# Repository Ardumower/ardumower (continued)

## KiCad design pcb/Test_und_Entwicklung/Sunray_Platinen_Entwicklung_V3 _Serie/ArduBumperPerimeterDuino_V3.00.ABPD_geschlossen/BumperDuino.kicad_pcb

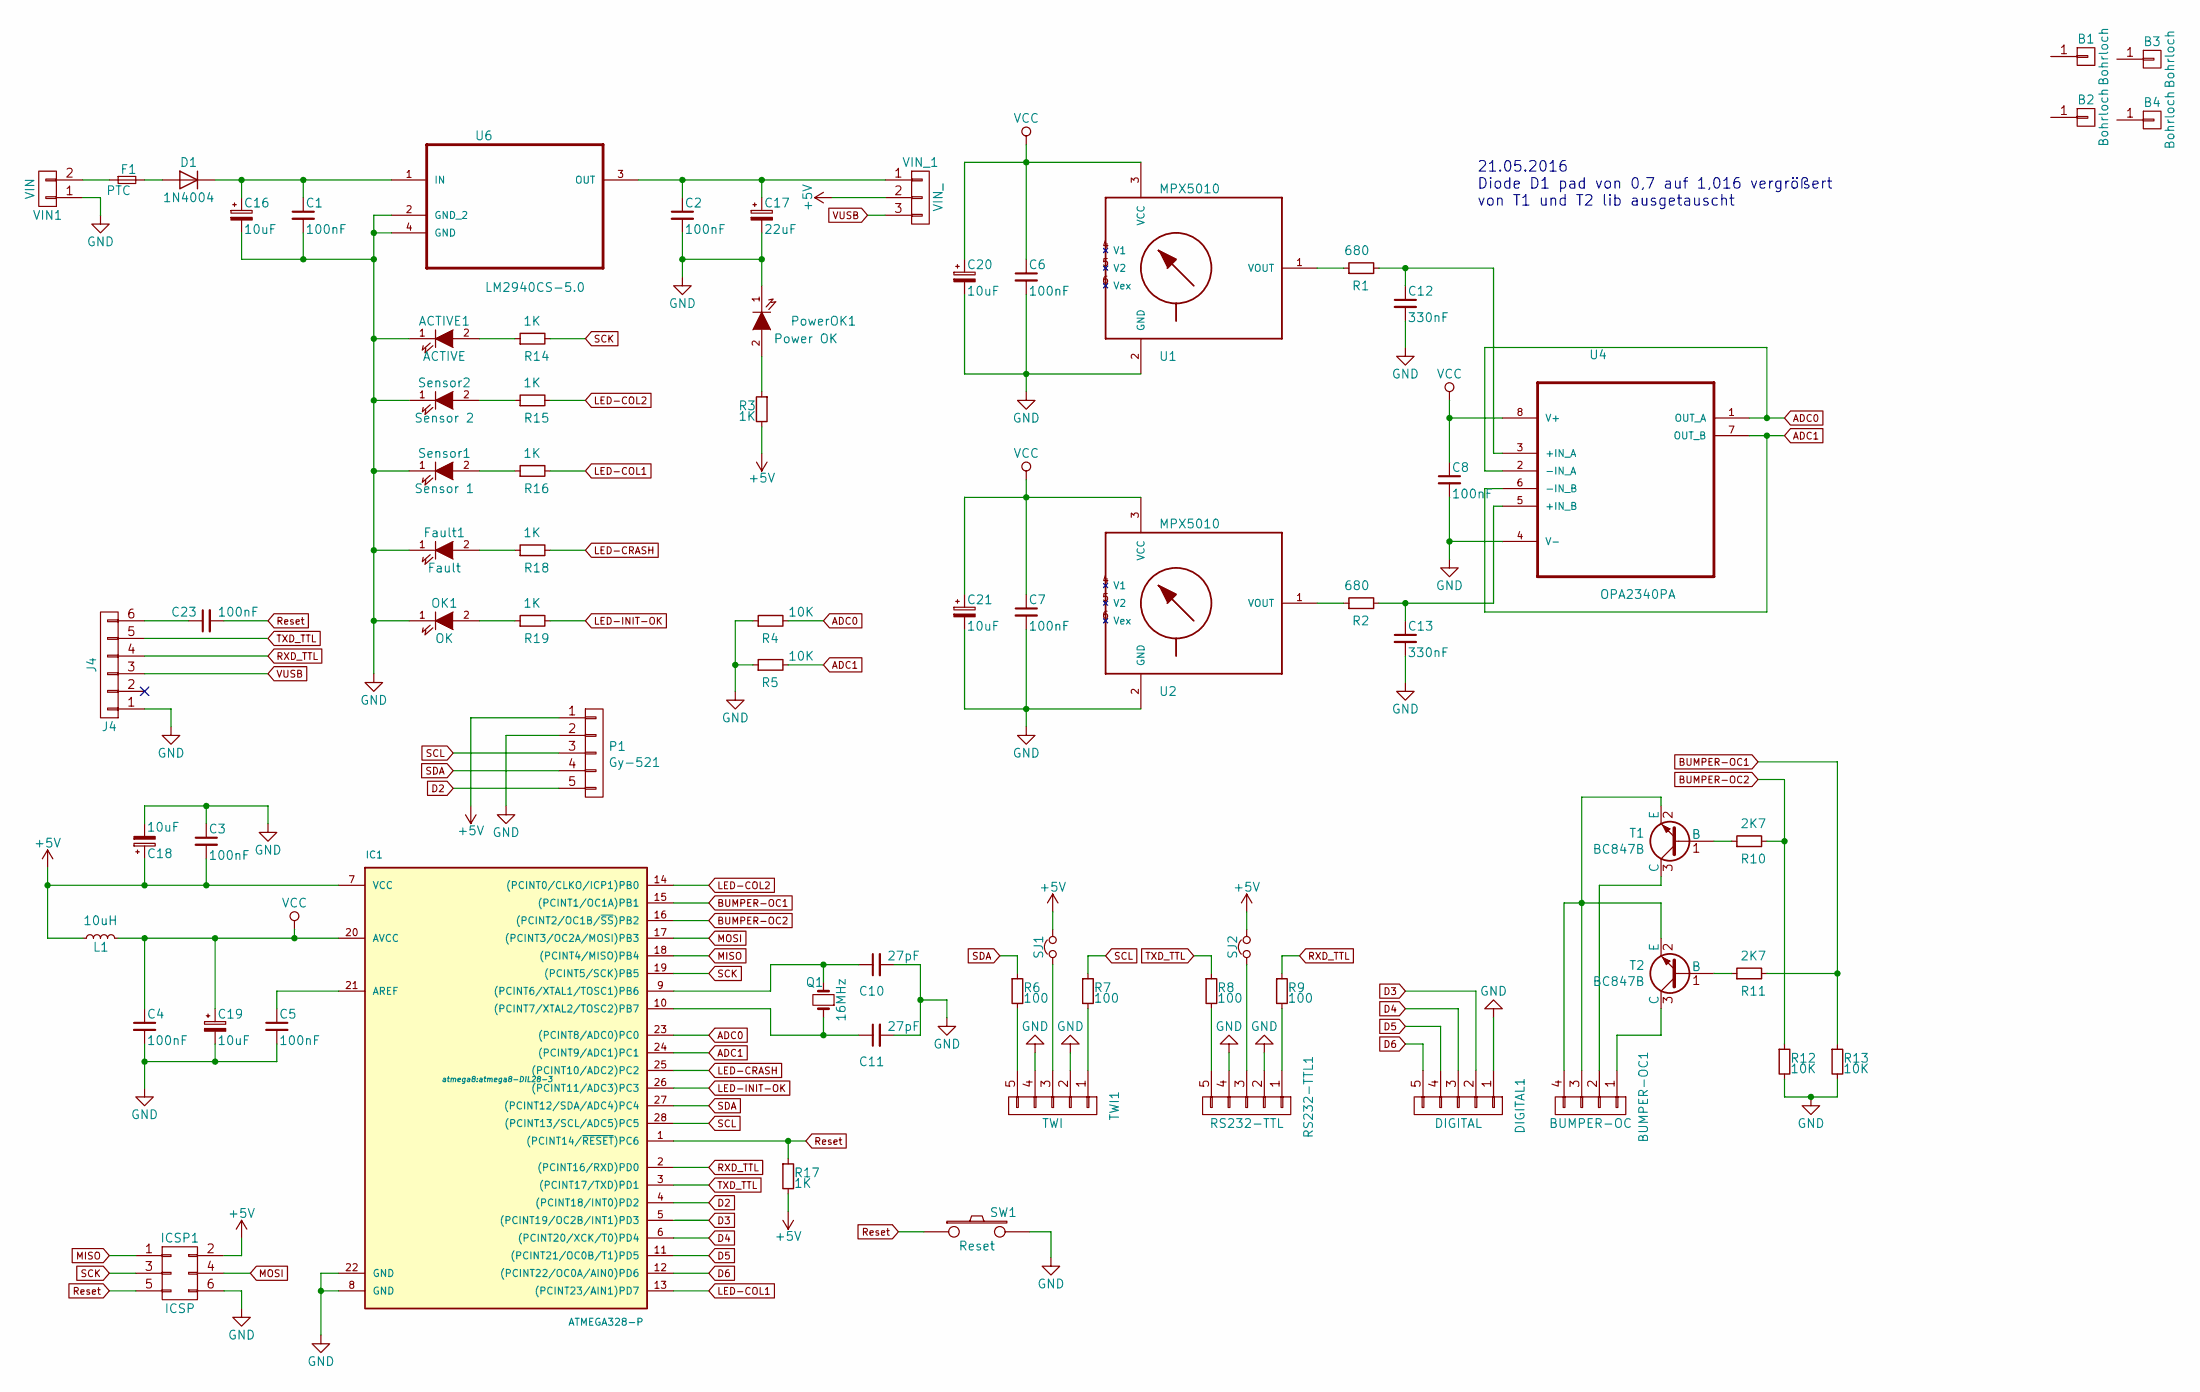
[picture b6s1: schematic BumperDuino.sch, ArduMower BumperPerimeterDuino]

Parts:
ACTIVE1: ACTIVE; LED_1206
B1, B2, B3, B4: Bohrloch; Bohrloch_3,2mm
BUMPER-OC1: BUMPER-OC; Pin_Header_Straight_1x04
C1, C2, C3, C4, C5, C6, C7, C8, C23: 100nF; C_0805
C10, C11: 27pF; C_0805
C12, C13: 330nF; C_0805
C16, C18, C19, C20, C21: 10uF; Elko_vert_11x5mm_RM2.5
C17: 22uF; Elko_vert_11x5mm_RM2.5
D1: 1N4004; Diode_DO-35_SOD27_Horizontal_RM10
DIGITAL1: DIGITAL; Pin_Header_Straight_1x05
F1: PTC; Fuse_SMD
Fault1: Fault; LED_1206
IC1: ATMEGA328-P; atmega8-DIL28-3
ICSP1: ICSP; Pin_Header_Straight_2x03
J4: J4; Pin_Header_Straight_1x06
L1: 10uH; Resistor_Horizontal_RM10mm
OK1: OK; LED_1206
P1: Gy-521; Pin_Header_Straight_1x05
PowerOK1: Power OK; LED_1206
Q1: 16MHz; Crystal_HC49-U_Vertical
R1, R2: 680; R_1206
R3, R14, R15, R16, R17, R18, R19: 1K; R_1206
R4, R5, R12, R13: 10K; R_1206
R6, R7, R8, R9: 100; R_1206
R10, R11: 2K7; R_1206
RS232-TTL1: RS232-TTL; Pin_Header_Straight_1x05
SJ1, SJ2: Jumper_NC_Small; Pin_Header_Straight_1x02
SW1: Reset; SW_SPST_FSMSM
Sensor1: Sensor 1; LED_1206
Sensor2: Sensor 2; LED_1206
T1, T2: BC847B; SOT-23
TWI1: TWI; Pin_Header_Straight_1x05
U1, U2: MPX5010; 867C-H
U4: OPA2340PA; DIP254P762X508-8
U6: LM2940CS-5.0; TO254P1435X464-4N
VIN1: VIN; Pin_Header_Straight_1x02
VIN_1: VIN_; Pin_Header_Straight_1x03

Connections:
+5V: C3.2, C18.1, IC1.7 (VCC), ICSP1.2, L1.1, P1.1, R3.2, R17.2, SJ1.2, SJ2.2, VIN_1.2
ADC0: IC1.23 ((PCINT8/ADC0)PC0), R4.2, U4.1 (OUT_A), U4.2 (-IN_A)
ADC1: IC1.24 ((PCINT9/ADC1)PC1), R5.2, U4.6 (-IN_B), U4.7 (OUT_B)
BUMPER-OC1: IC1.15 ((PCINT1/OC1A)PB1), R11.2, R13.1
BUMPER-OC2: IC1.16 ((PCINT2/OC1B/~SS~)PB2), R10.2, R12.1
D2: IC1.4 ((PCINT18/INT0)PD2), P1.5
D3: DIGITAL1.2, IC1.5 ((PCINT19/OC2B/INT1)PD3)
D4: DIGITAL1.3, IC1.6 ((PCINT20/XCK/T0)PD4)
D5: DIGITAL1.4, IC1.11 ((PCINT21/OC0B/T1)PD5)
D6: DIGITAL1.5, IC1.12 ((PCINT22/OC0A/AIN0)PD6)
GND: ACTIVE1.1 (K), C1.2, C2.2, C3.1, C4.2, C5.2, C6.2, C7.2, C8.2, C10.2, C11.2, C12.2, C13.2, C16.2, C17.2, C18.2, C19.2, C20.2, C21.2, DIGITAL1.1, Fault1.1 (K), IC1.8 (GND), IC1.22 (GND), ICSP1.6, J4.1, OK1.1 (K), P1.2, PowerOK1.1 (K), R4.1, R5.1, R12.2, R13.2, RS232-TTL1.2, RS232-TTL1.4, SW1.2, Sensor1.1 (K), Sensor2.1 (K), TWI1.2, TWI1.4, U1.2 (GND), U2.2 (GND), U4.4 (V-), U6.2 (GND_2), U6.4 (GND), VIN1.1
LED-COL1: IC1.13 ((PCINT23/AIN1)PD7), R16.2
LED-COL2: IC1.14 ((PCINT0/CLKO/ICP1)PB0), R15.2
LED-CRASH: IC1.25 ((PCINT10/ADC2)PC2), R18.2
LED-INIT-OK: IC1.26 ((PCINT11/ADC3)PC3), R19.2
MISO: IC1.18 ((PCINT4/MISO)PB4), ICSP1.1
MOSI: IC1.17 ((PCINT3/OC2A/MOSI)PB3), ICSP1.4
unnamed: ACTIVE1.2 (A), R14.1
unnamed: BUMPER-OC1.1, T2.3 (C)
unnamed: BUMPER-OC1.2, T1.3 (C)
unnamed: BUMPER-OC1.3, BUMPER-OC1.4, T1.2 (E), T2.2 (E)
unnamed: C1.1, C16.1, D1.1 (K), U6.1 (IN)
unnamed: C5.1, IC1.21 (AREF)
unnamed: C10.1, IC1.9 ((PCINT6/XTAL1/TOSC1)PB6), Q1.2
unnamed: C11.1, IC1.10 ((PCINT7/XTAL2/TOSC2)PB7), Q1.1
unnamed: C12.1, R1.2, U4.3 (+IN_A)
unnamed: C13.1, R2.2, U4.5 (+IN_B)
unnamed: C2.1, C17.1, U6.3 (OUT), VIN_1.1
unnamed: C23.1, J4.6
unnamed: D1.2 (A), F1.2
unnamed: F1.1, VIN1.2
unnamed: Fault1.2 (A), R18.1
unnamed: OK1.2 (A), R19.1
unnamed: PowerOK1.2 (A), R3.1
unnamed: R1.1, U1.1 (VOUT)
unnamed: R2.1, U2.1 (VOUT)
unnamed: R6.2, TWI1.5
unnamed: R7.2, TWI1.1
unnamed: R8.2, RS232-TTL1.5
unnamed: R9.2, RS232-TTL1.1
unnamed: R10.1, T1.1 (B)
unnamed: R11.1, T2.1 (B)
unnamed: R15.1, Sensor2.2 (A)
unnamed: R16.1, Sensor1.2 (A)
unnamed: RS232-TTL1.3, SJ2.1
unnamed: SJ1.1, TWI1.3
RXD_TTL: IC1.2 ((PCINT16/RXD)PD0), J4.4, R9.1
Reset: C23.2, IC1.1 ((PCINT14/~RESET~)PC6), ICSP1.5, R17.1, SW1.1
SCK: IC1.19 ((PCINT5/SCK)PB5), ICSP1.3, R14.2
SCL: IC1.28 ((PCINT13/SCL/ADC5)PC5), P1.3, R7.1
SDA: IC1.27 ((PCINT12/SDA/ADC4)PC4), P1.4, R6.1
TXD_TTL: IC1.3 ((PCINT17/TXD)PD1), J4.5, R8.1
VCC: C4.1, C6.1, C7.1, C8.1, C19.1, C20.1, C21.1, IC1.20 (AVCC), L1.2, U1.3 (VCC), U2.3 (VCC), U4.8 (V+)
VUSB: J4.3, VIN_1.3

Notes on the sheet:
21.05.2016 Diode D1 pad von 0,7 auf 1,016 vergrößert von T1 und T2 lib ausgetauscht

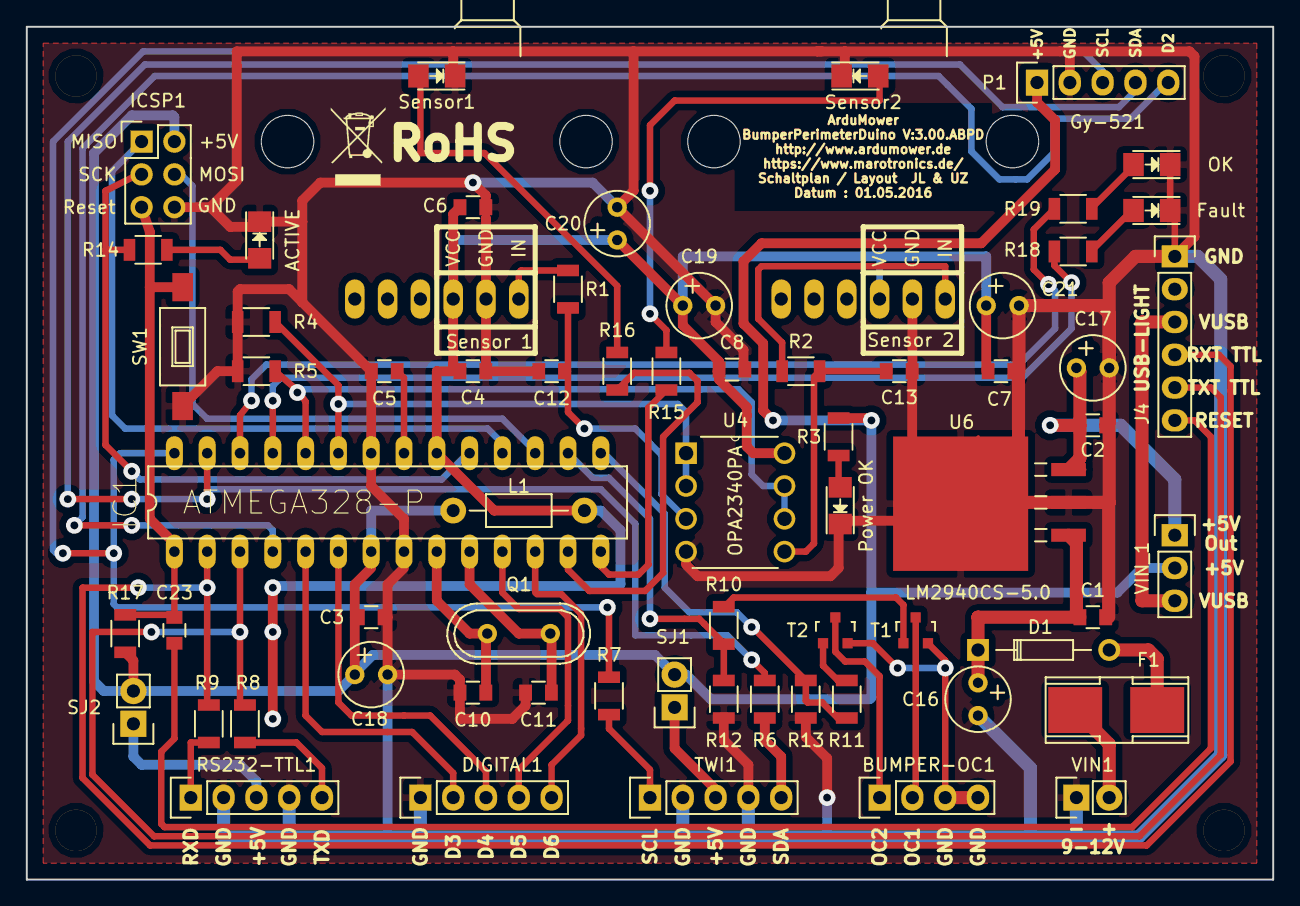
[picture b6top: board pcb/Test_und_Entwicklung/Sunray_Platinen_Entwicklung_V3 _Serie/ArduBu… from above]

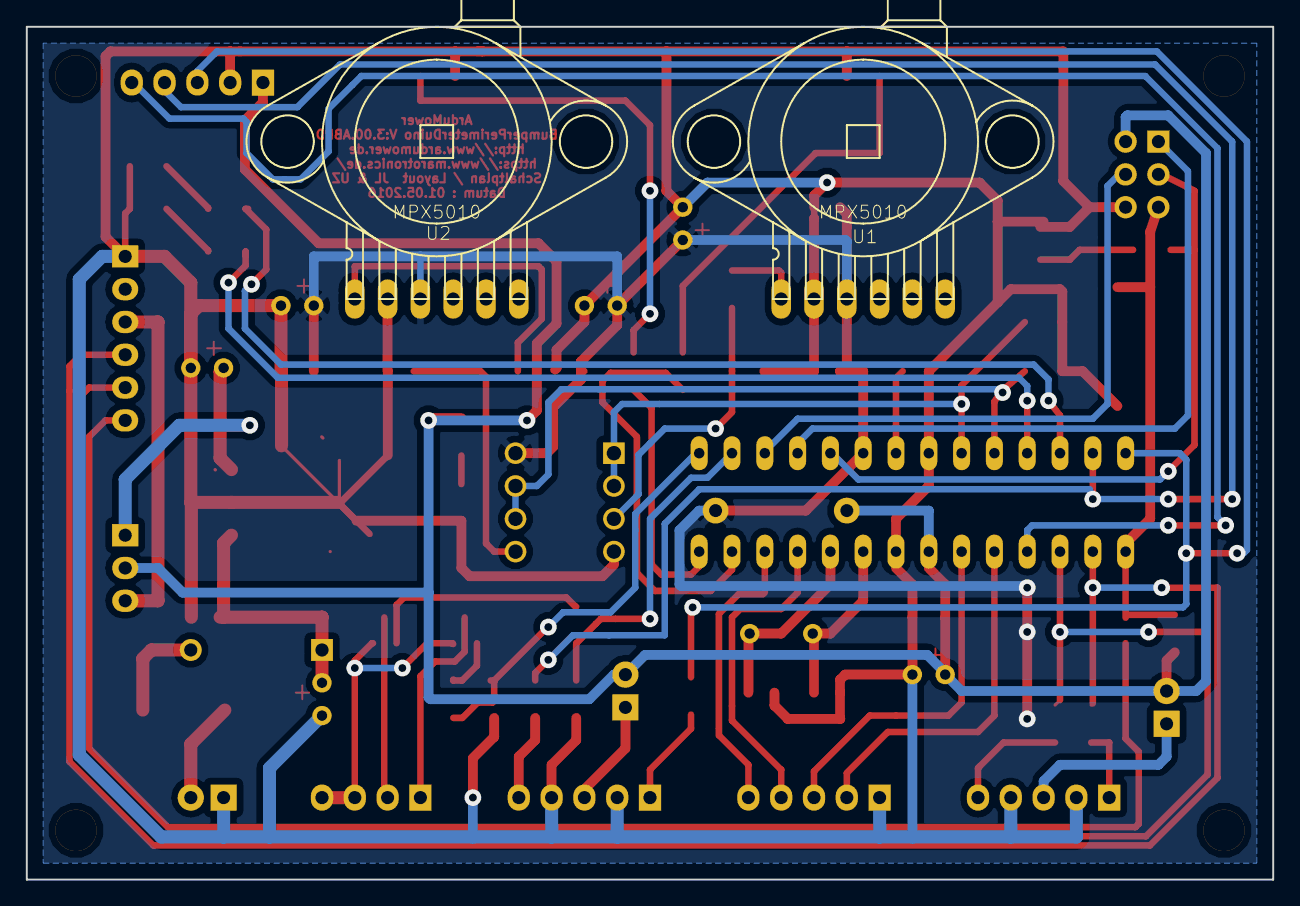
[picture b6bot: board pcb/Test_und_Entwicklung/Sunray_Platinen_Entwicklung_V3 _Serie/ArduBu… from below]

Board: 2 copper layers, 96.5 x 66.0 mm, 71 parts (2 on the bottom side), 54 nets.
